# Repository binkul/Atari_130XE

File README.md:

# Schema of Atari 130XE C070067 REV B
# 2 x 4464 (4 bit RAM)

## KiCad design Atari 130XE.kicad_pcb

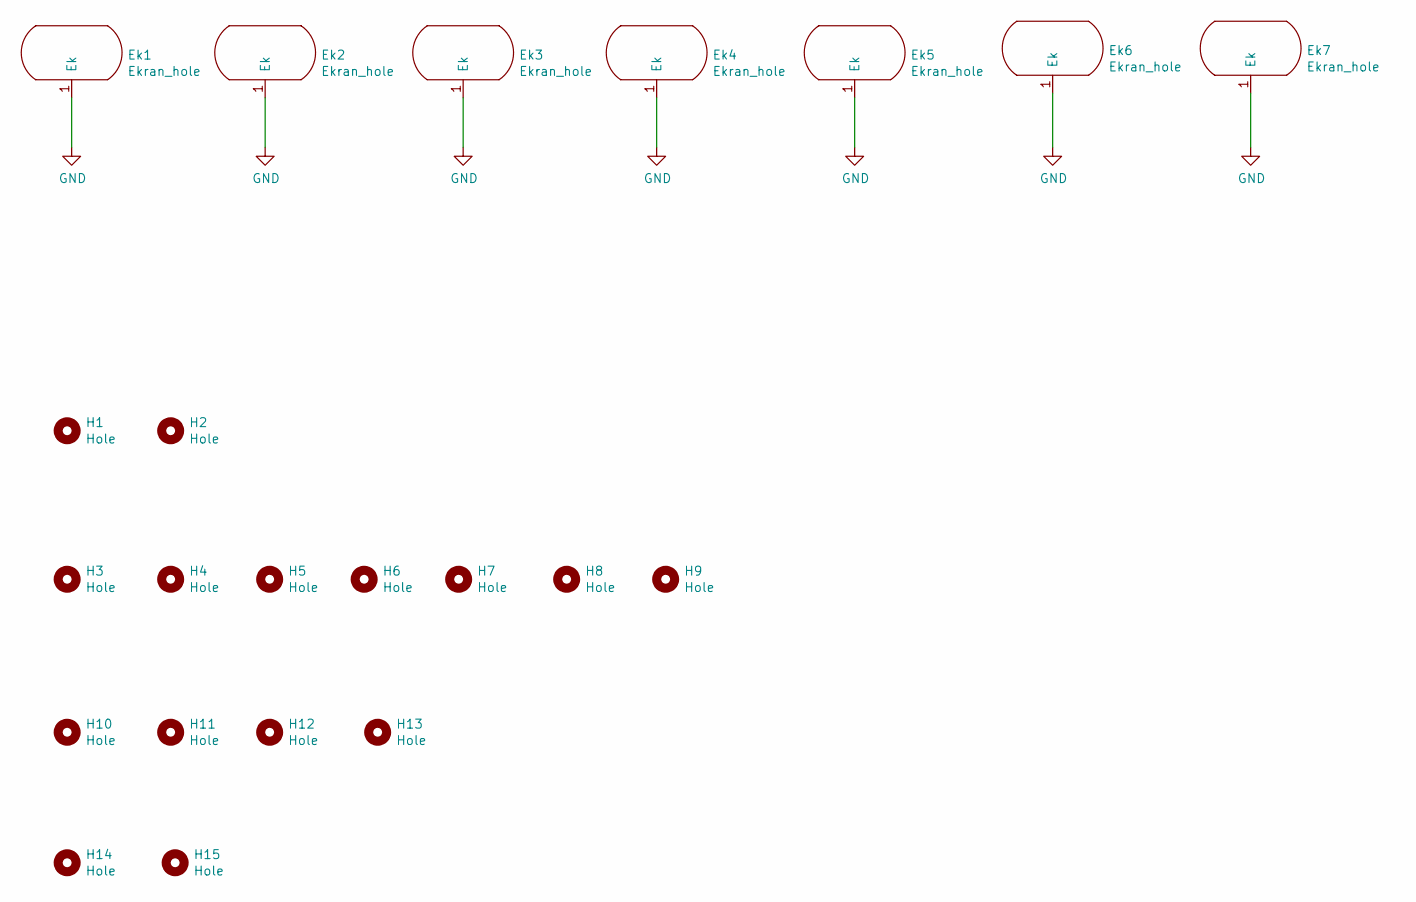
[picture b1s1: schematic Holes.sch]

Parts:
Ek1, Ek2, Ek3, Ek4, Ek5, Ek6, Ek7: Ekran_hole; Ekran_GND
H1, H2: Hole; Medium_hole
H3, H4, H5, H6, H7, H8, H9: Hole; Hole_3.4mm
H10, H11, H12, H13: Hole; Hole_4.4mm
H14, H15: Hole; MountingHole_4.5mm

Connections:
GND: Ek1.1, Ek2.1, Ek3.1, Ek4.1, Ek5.1, Ek6.1, Ek7.1; also elsewhere on the board

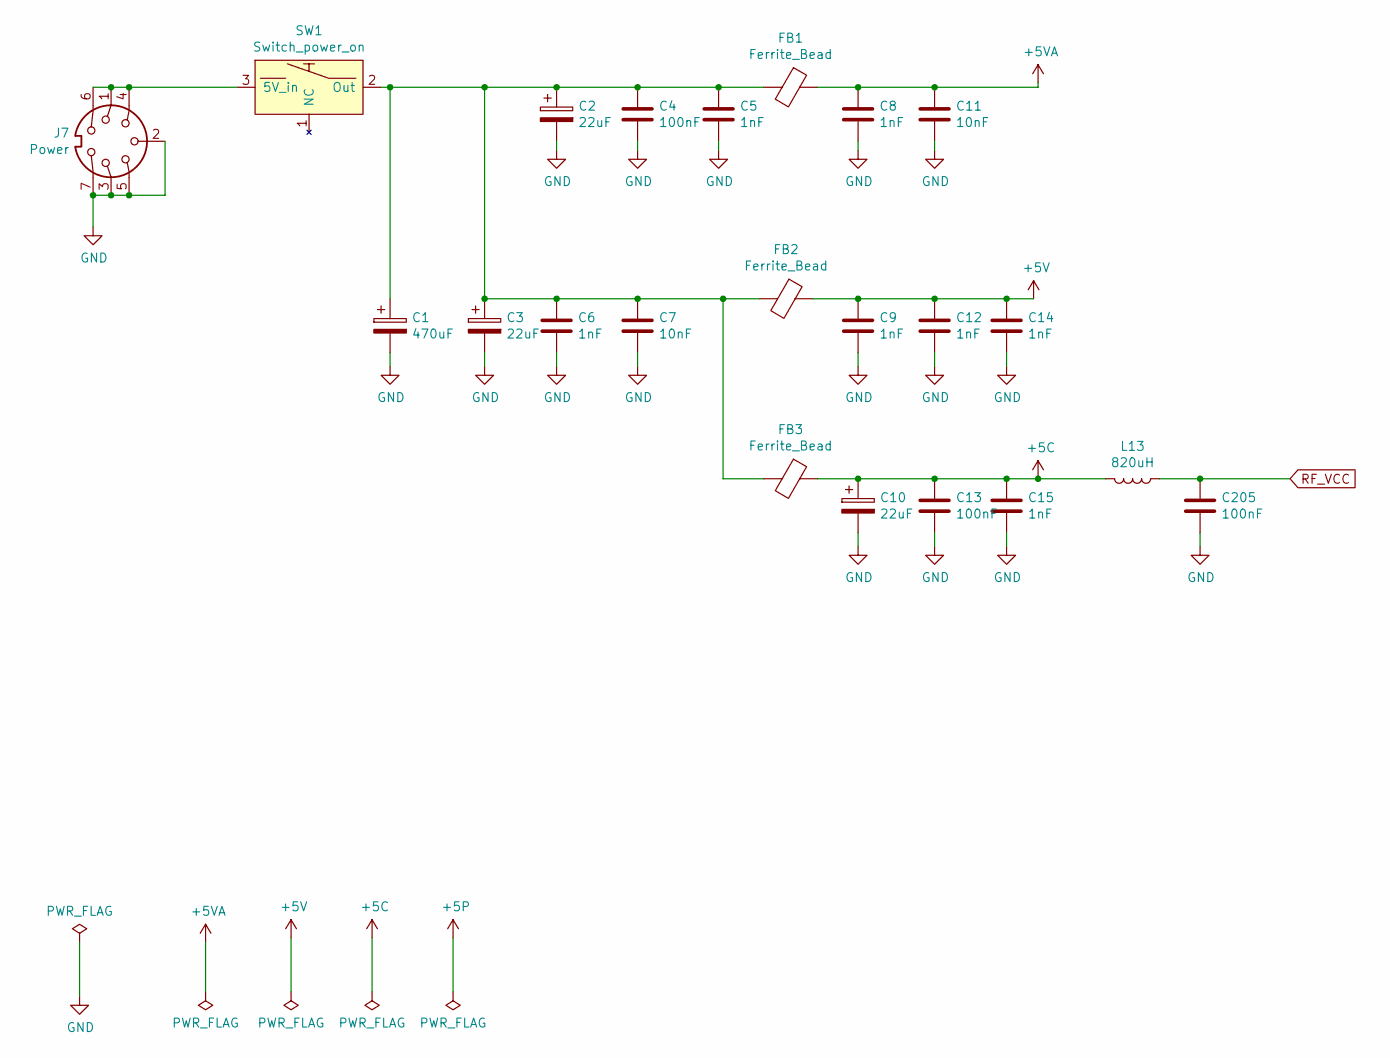
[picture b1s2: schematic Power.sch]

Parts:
C1: 470uF; CP_Radial_D8.0mm_P3.80mm
C2, C3, C10: 22uF; CP_Radial_D6.3mm_P2.50mm
C4, C13, C205: 100nF; C_Axial_L5.1mm_D2.5mm_P12.50mm_Horizontal
C5, C6, C8, C9, C12, C14, C15: 1nF; C_Axial_L5.1mm_D2.5mm_P12.50mm_Horizontal
C7, C11: 10nF; C_Axial_L5.1mm_D2.5mm_P12.50mm_Horizontal
FB1, FB2, FB3: Ferrite_Bead; L_Axial_L7.0mm_D3.3mm_P12.50mm_Horizontal_Fastron_MICC
J7: Power; DIN_7_pin
L13: 820uH; L_Axial_L7.0mm_D3.3mm_P12.50mm_Horizontal_Fastron_MICC
SW1: Switch_power_on; Switch_ON-OFF

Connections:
+5C: C10.1, C13.1, C15.1, FB3.1, L13.2; also elsewhere on the board
+5V: C9.1, C12.1, C14.1, FB2.1
+5VA: C8.1, C11.1, FB1.1; also elsewhere on the board
GND: C1.2, C2.2, C3.2, C4.2, C5.2, C6.2, C7.2, C8.2, C9.2, C10.2, C11.2, C12.2, C13.2, C14.2, C15.2, C205.2, J7.2, J7.3, J7.5, J7.7; also elsewhere on the board
unnamed: C1.1, C2.1, C3.1, C4.1, C5.1, C6.1, C7.1, FB1.2, FB2.2, FB3.2, SW1.2 (Out)
unnamed: J7.1, J7.4, J7.6, SW1.3 (5V_in)
RF_VCC: C205.1, L13.1; also elsewhere on the board

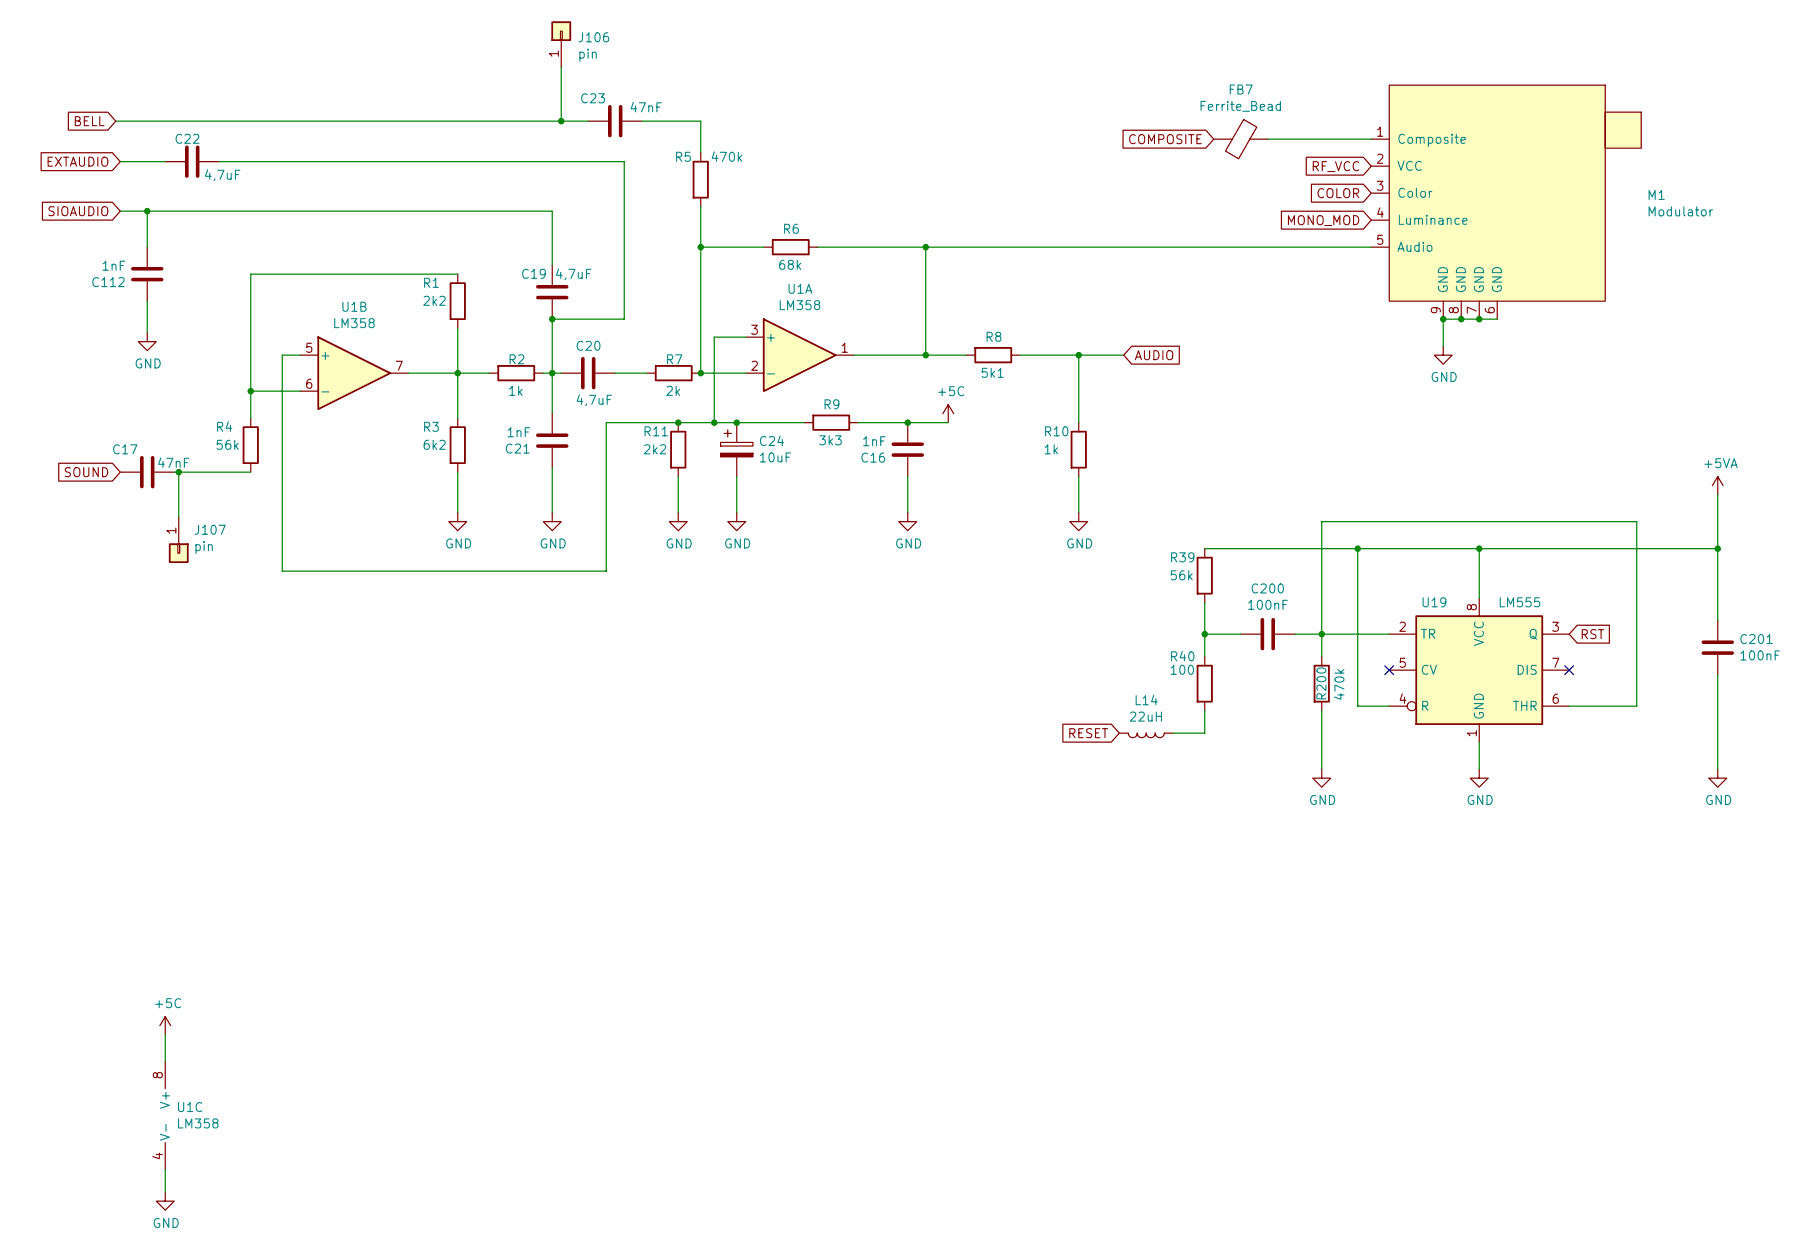
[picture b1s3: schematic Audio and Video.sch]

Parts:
C16, C21, C112: 1nF; C_Axial_L5.1mm_D2.5mm_P12.50mm_Horizontal
C17, C23: 47nF; C_Axial_L5.1mm_D2.5mm_P12.50mm_Horizontal
C19, C20, C22: 4,7uF; CP_Radial_D8.0mm_P3.50mm
C24: 10uF; CP_Axial_L11.0mm_D6.0mm_P18.00mm_Horizontal
C200, C201: 100nF; C_Axial_L5.1mm_D2.5mm_P12.50mm_Horizontal
FB7: Ferrite_Bead; L_Axial_L7.0mm_D3.3mm_P12.50mm_Horizontal_Fastron_MICC
J106, J107: pin; PinHeader_1x01_P2.00mm_Vertical
L14: 22uH; L_Axial_L7.0mm_D3.3mm_P12.50mm_Horizontal_Fastron_MICC
M1: Modulator; Modulator_TV
R1, R11: 2k2; R_Axial_DIN0207_L3.6mm_D2.2mm_P10.16mm_Horizontal
R2, R10: 1k; R_Axial_DIN0207_L3.6mm_D2.2mm_P10.16mm_Horizontal
R3: 6k2; R_Axial_DIN0207_L3.6mm_D2.2mm_P10.16mm_Horizontal
R4, R39: 56k; R_Axial_DIN0207_L3.6mm_D2.2mm_P10.16mm_Horizontal
R5, R200: 470k; R_Axial_DIN0207_L3.6mm_D2.2mm_P10.16mm_Horizontal
R6: 68k; R_Axial_DIN0207_L3.6mm_D2.2mm_P10.16mm_Horizontal
R7: 2k; R_Axial_DIN0207_L3.6mm_D2.2mm_P10.16mm_Horizontal
R8: 5k1; R_Axial_DIN0207_L3.6mm_D2.2mm_P10.16mm_Horizontal
R9: 3k3; R_Axial_DIN0207_L3.6mm_D2.2mm_P10.16mm_Horizontal
R40: 100; R_Axial_DIN0207_L3.6mm_D2.2mm_P10.16mm_Horizontal
U1: LM358; DIP-8_W7.62mm_Socket
U19: LM555; DIP-8_W7.62mm_Socket

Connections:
+5C: C16.2, R9.1, U1.8 (V+); also elsewhere on the board
+5VA: C201.1, R39.1, U19.4 (R), U19.8 (VCC); also elsewhere on the board
AUDIO: R8.1, R10.1; also elsewhere on the board
BELL: C23.2, J106.1; also elsewhere on the board
COLOR: M1.3 (Color); also elsewhere on the board
COMPOSITE: FB7.2; also elsewhere on the board
EXTAUDIO: C22.1; also elsewhere on the board
GND: C16.1, C21.1, C24.2, C112.1, C201.2, M1.6 (GND), M1.7 (GND), M1.8 (GND), M1.9 (GND), R3.2, R10.2, R11.2, R200.2, U1.4 (V-), U19.1 (GND); also elsewhere on the board
MONO_MOD: M1.4 (Luminance); also elsewhere on the board
unnamed: C17.1, J107.1, R4.2
unnamed: C19.1, C20.2, C21.2, C22.2, R2.1
unnamed: C20.1, R7.2
unnamed: C23.1, R5.1
unnamed: C24.1, R9.2, R11.1, U1.3 (+), U1.5 (+)
unnamed: C200.1, R200.1, U19.2 (TR), U19.6 (THR)
unnamed: C200.2, R39.2, R40.1
unnamed: FB7.1, M1.1 (Composite)
unnamed: L14.1, R40.2
unnamed: M1.5 (Audio), R6.1, R8.2, U1.1
unnamed: R1.1, R4.1, U1.6 (-)
unnamed: R1.2, R2.2, R3.1, U1.7
unnamed: R5.2, R6.2, R7.1, U1.2 (-)
RESET: L14.2; also elsewhere on the board
RF_VCC: M1.2 (VCC); also elsewhere on the board
RST: U19.3 (Q); also elsewhere on the board
SIOAUDIO: C19.2, C112.2; also elsewhere on the board
SOUND: C17.2; also elsewhere on the board

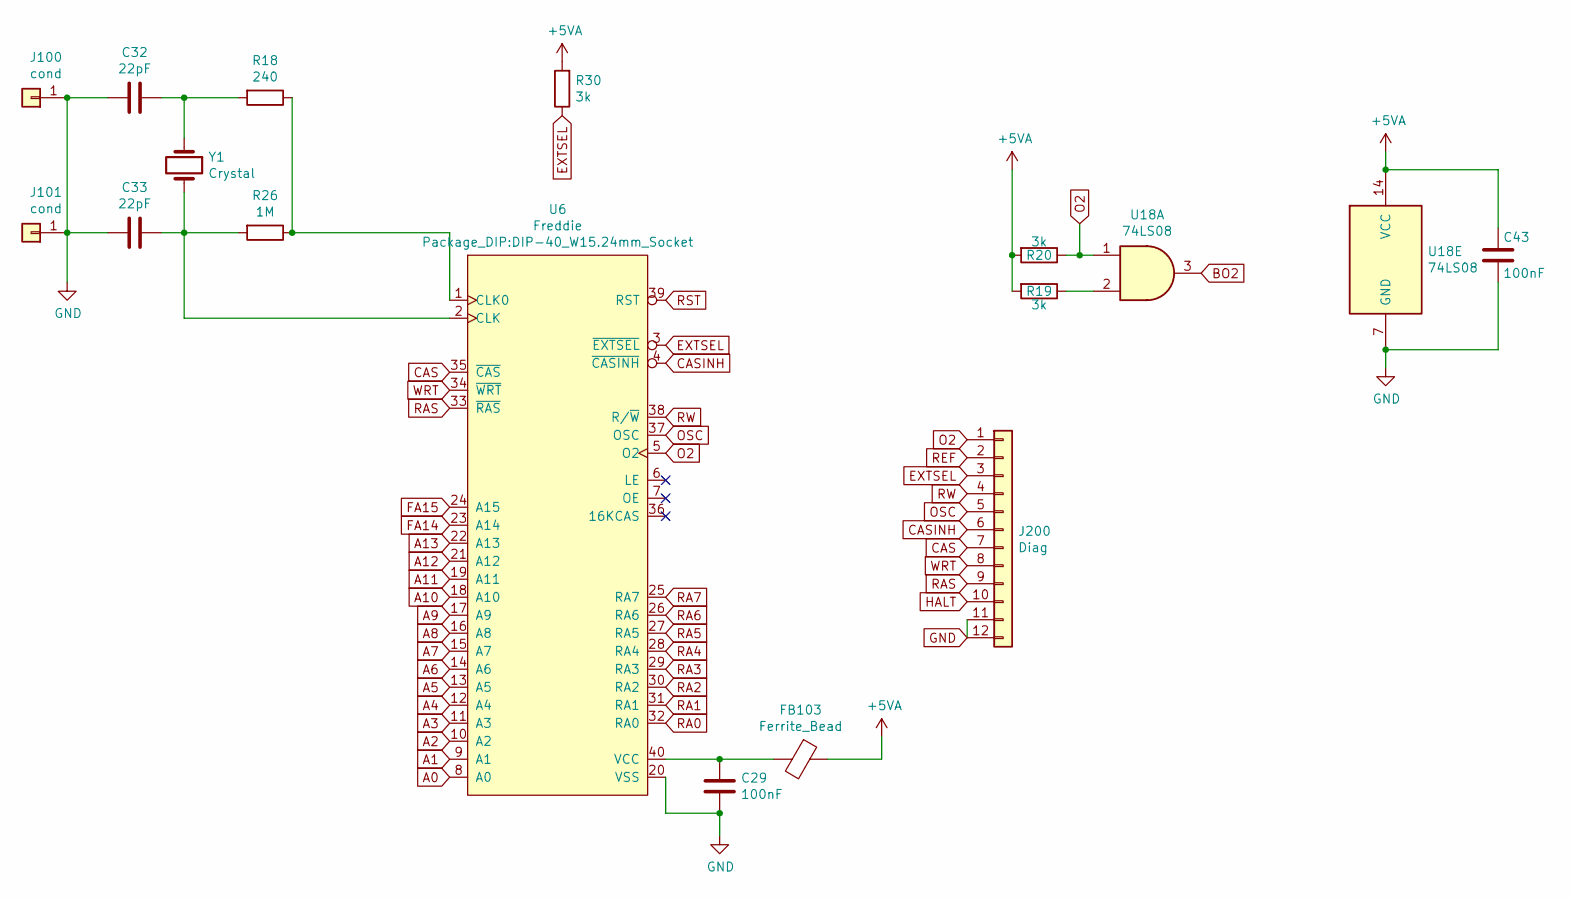
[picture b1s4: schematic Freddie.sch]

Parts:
C29, C43: 100nF; C_Axial_L5.1mm_D2.5mm_P12.50mm_Horizontal
C32, C33: 22pF; C_Axial_L5.1mm_D2.5mm_P12.50mm_Horizontal
FB103: Ferrite_Bead; L_Axial_L7.0mm_D3.3mm_P12.50mm_Horizontal_Fastron_MICC
J100, J101: cond; PinHeader_1x01_P2.00mm_Vertical
J200: Diag; PinHeader_1x12_P2.54mm_Vertical
R18: 240; R_Axial_DIN0207_L6.3mm_D2.5mm_P10.16mm_Horizontal
R19, R20, R30: 3k; R_Axial_DIN0207_L3.6mm_D2.2mm_P10.16mm_Horizontal
R26: 1M; R_Axial_DIN0207_L6.3mm_D2.5mm_P10.16mm_Horizontal
U6: Freddie; DIP-40_W15.24mm_Socket
U18: 74LS08; DIP-14_W7.62mm_Socket
Y1: Crystal; Crystal_HC18-U_Vertical

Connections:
+5VA: C43.1, FB103.1, R19.2, R20.2, R30.2, U18.14 (VCC); also elsewhere on the board
A0: U6.8 (A0); also elsewhere on the board
A1: U6.9 (A1); also elsewhere on the board
A2: U6.10 (A2); also elsewhere on the board
A3: U6.11 (A3); also elsewhere on the board
A4: U6.12 (A4); also elsewhere on the board
A5: U6.13 (A5); also elsewhere on the board
A6: U6.14 (A6); also elsewhere on the board
A7: U6.15 (A7); also elsewhere on the board
A8: U6.16 (A8); also elsewhere on the board
A9: U6.17 (A9); also elsewhere on the board
A10: U6.18 (A10); also elsewhere on the board
A11: U6.19 (A11); also elsewhere on the board
A12: U6.21 (A12); also elsewhere on the board
A13: U6.22 (A13); also elsewhere on the board
BO2: U18.3; also elsewhere on the board
CAS: J200.7, U6.35 (~CAS); also elsewhere on the board
CASINH: J200.6, U6.4 (~CASINH); also elsewhere on the board
EXTSEL: J200.3, R30.1, U6.3 (~EXTSEL); also elsewhere on the board
FA14: U6.23 (A14); also elsewhere on the board
FA15: U6.24 (A15); also elsewhere on the board
GND: C29.2, C32.2, C33.2, C43.2, J100.1, J101.1, J200.11, J200.12, U6.20 (VSS), U18.7 (GND); also elsewhere on the board
HALT: J200.10; also elsewhere on the board
unnamed: C29.1, FB103.2, U6.40 (VCC)
unnamed: C32.1, R18.2, Y1.1
unnamed: C33.1, R26.2, U6.2 (CLK), Y1.2
unnamed: R18.1, R26.1, U6.1 (CLK0)
unnamed: R19.1, U18.2
O2: J200.1, R20.1, U6.5 (O2), U18.1; also elsewhere on the board
OSC: J200.5, U6.37 (OSC); also elsewhere on the board
RA0: U6.32 (RA0); also elsewhere on the board
RA1: U6.31 (RA1); also elsewhere on the board
RA2: U6.30 (RA2); also elsewhere on the board
RA3: U6.29 (RA3); also elsewhere on the board
RA4: U6.28 (RA4); also elsewhere on the board
RA5: U6.27 (RA5); also elsewhere on the board
RA6: U6.26 (RA6); also elsewhere on the board
RA7: U6.25 (RA7); also elsewhere on the board
RAS: J200.9, U6.33 (~RAS); also elsewhere on the board
REF: J200.2; also elsewhere on the board
RST: U6.39 (RST); also elsewhere on the board
RW: J200.4, U6.38 (R/~W); also elsewhere on the board
WRT: J200.8, U6.34 (~WRT); also elsewhere on the board

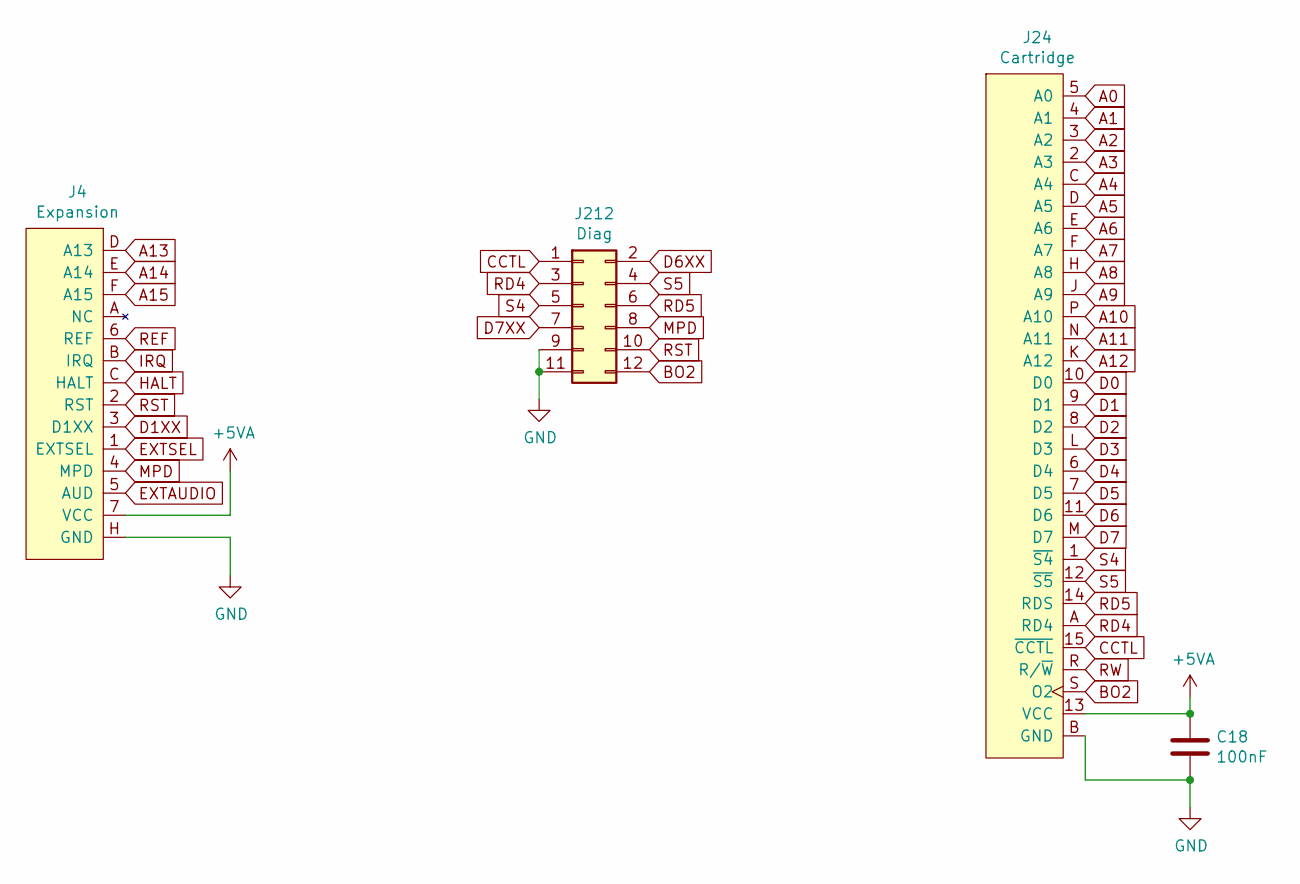
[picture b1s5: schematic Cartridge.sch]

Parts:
C18: 100nF; C_Axial_L5.1mm_D2.5mm_P12.50mm_Horizontal
J4: Expansion; Expansion_Slot
J24: Cartridge; Cartridge_Slot
J212: Diag; PinHeader_2x06_P2.54mm_Vertical

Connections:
+5VA: C18.1, J4.7 (VCC), J24.13 (VCC); also elsewhere on the board
A0: J24.5 (A0); also elsewhere on the board
A1: J24.4 (A1); also elsewhere on the board
A2: J24.3 (A2); also elsewhere on the board
A3: J24.2 (A3); also elsewhere on the board
A4: J24.C (A4); also elsewhere on the board
A5: J24.D (A5); also elsewhere on the board
A6: J24.E (A6); also elsewhere on the board
A7: J24.F (A7); also elsewhere on the board
A8: J24.H (A8); also elsewhere on the board
A9: J24.J (A9); also elsewhere on the board
A10: J24.P (A10); also elsewhere on the board
A11: J24.N (A11); also elsewhere on the board
A12: J24.K (A12); also elsewhere on the board
A13: J4.D (A13); also elsewhere on the board
A14: J4.E (A14); also elsewhere on the board
A15: J4.F (A15); also elsewhere on the board
BO2: J24.S (O2), J212.12; also elsewhere on the board
CCTL: J24.15 (~CCTL), J212.1; also elsewhere on the board
D0: J24.10 (D0); also elsewhere on the board
D1: J24.9 (D1); also elsewhere on the board
D1XX: J4.3 (D1XX); also elsewhere on the board
D2: J24.8 (D2); also elsewhere on the board
D3: J24.L (D3); also elsewhere on the board
D4: J24.6 (D4); also elsewhere on the board
D5: J24.7 (D5); also elsewhere on the board
D6: J24.11 (D6); also elsewhere on the board
D6XX: J212.2; also elsewhere on the board
D7: J24.M (D7); also elsewhere on the board
D7XX: J212.7; also elsewhere on the board
EXTAUDIO: J4.5 (AUD); also elsewhere on the board
EXTSEL: J4.1 (EXTSEL); also elsewhere on the board
GND: C18.2, J4.H (GND), J24.B (GND), J212.9, J212.11; also elsewhere on the board
HALT: J4.C (HALT); also elsewhere on the board
IRQ: J4.B (IRQ); also elsewhere on the board
MPD: J4.4 (MPD), J212.8; also elsewhere on the board
RD4: J24.A (RD4), J212.3; also elsewhere on the board
RD5: J24.14 (RDS), J212.6; also elsewhere on the board
REF: J4.6 (REF); also elsewhere on the board
RST: J4.2 (RST), J212.10; also elsewhere on the board
RW: J24.R (R/~W); also elsewhere on the board
S4: J24.1 (~S4), J212.5; also elsewhere on the board
S5: J24.12 (~S5), J212.4; also elsewhere on the board

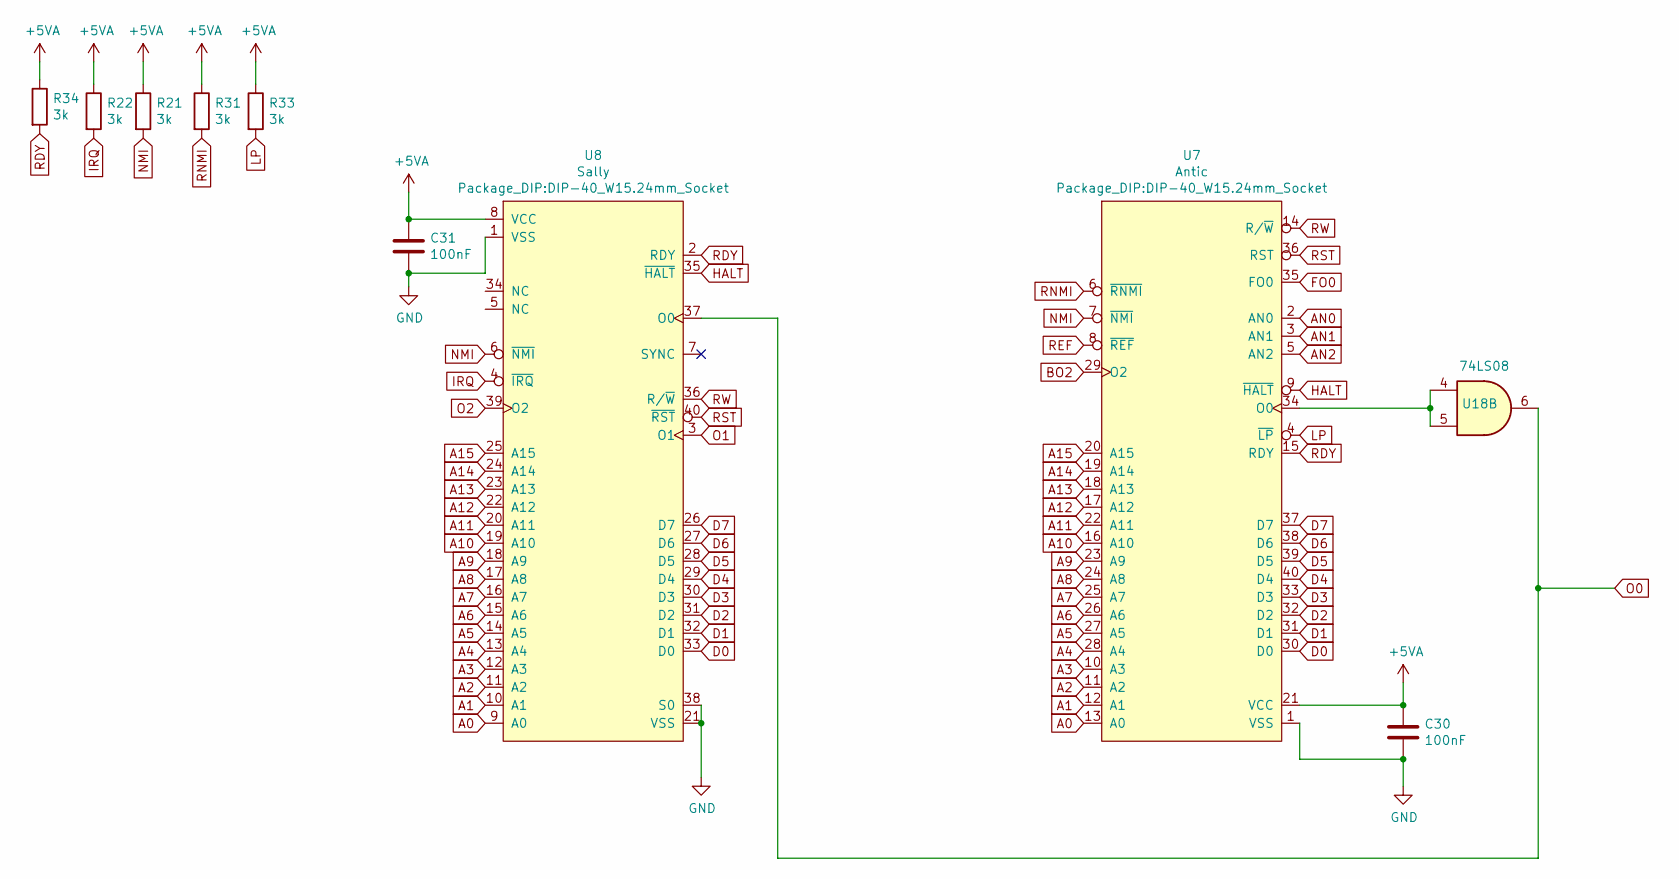
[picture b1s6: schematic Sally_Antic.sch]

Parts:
C30, C31: 100nF; C_Axial_L5.1mm_D2.5mm_P12.50mm_Horizontal
R21, R22, R31, R33, R34: 3k; R_Axial_DIN0207_L3.6mm_D2.2mm_P10.16mm_Horizontal
U7: Antic; DIP-40_W15.24mm_Socket
U8: Sally; DIP-40_W15.24mm_Socket
U18: 74LS08; DIP-14_W7.62mm_Socket

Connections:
+5VA: C30.1, C31.1, R21.1, R22.1, R31.1, R33.1, R34.1, U7.21 (VCC), U8.8 (VCC); also elsewhere on the board
A0: U7.13 (A0), U8.9 (A0); also elsewhere on the board
A1: U7.12 (A1), U8.10 (A1); also elsewhere on the board
A2: U7.11 (A2), U8.11 (A2); also elsewhere on the board
A3: U7.10 (A3), U8.12 (A3); also elsewhere on the board
A4: U7.28 (A4), U8.13 (A4); also elsewhere on the board
A5: U7.27 (A5), U8.14 (A5); also elsewhere on the board
A6: U7.26 (A6), U8.15 (A6); also elsewhere on the board
A7: U7.25 (A7), U8.16 (A7); also elsewhere on the board
A8: U7.24 (A8), U8.17 (A8); also elsewhere on the board
A9: U7.23 (A9), U8.18 (A9); also elsewhere on the board
A10: U7.16 (A10), U8.19 (A10); also elsewhere on the board
A11: U7.22 (A11), U8.20 (A11); also elsewhere on the board
A12: U7.17 (A12), U8.22 (A12); also elsewhere on the board
A13: U7.18 (A13), U8.23 (A13); also elsewhere on the board
A14: U7.19 (A14), U8.24 (A14); also elsewhere on the board
A15: U7.20 (A15), U8.25 (A15); also elsewhere on the board
AN0: U7.2 (AN0); also elsewhere on the board
AN1: U7.3 (AN1); also elsewhere on the board
AN2: U7.5 (AN2); also elsewhere on the board
BO2: U7.29 (O2); also elsewhere on the board
D0: U7.30 (D0), U8.33 (D0); also elsewhere on the board
D1: U7.31 (D1), U8.32 (D1); also elsewhere on the board
D2: U7.32 (D2), U8.31 (D2); also elsewhere on the board
D3: U7.33 (D3), U8.30 (D3); also elsewhere on the board
D4: U7.40 (D4), U8.29 (D4); also elsewhere on the board
D5: U7.39 (D5), U8.28 (D5); also elsewhere on the board
D6: U7.38 (D6), U8.27 (D6); also elsewhere on the board
D7: U7.37 (D7), U8.26 (D7); also elsewhere on the board
FO0: U7.35 (FO0); also elsewhere on the board
GND: C30.2, C31.2, U7.1 (VSS), U8.1 (VSS), U8.21 (VSS), U8.38 (S0); also elsewhere on the board
HALT: U7.9 (~HALT), U8.35 (~HALT); also elsewhere on the board
IRQ: R22.2, U8.4 (~IRQ); also elsewhere on the board
LP: R33.2, U7.4 (~LP); also elsewhere on the board
NMI: R21.2, U7.7 (~NMI), U8.6 (~NMI)
unnamed: U7.34 (O0), U18.4, U18.5
O0: U8.37 (O0), U18.6
O1: U8.3 (O1); also elsewhere on the board
O2: U8.39 (O2); also elsewhere on the board
RDY: R34.2, U7.15 (RDY), U8.2 (RDY)
REF: U7.8 (~REF); also elsewhere on the board
RNMI: R31.2, U7.6 (~RNMI)
RST: U7.36 (RST), U8.40 (~RST); also elsewhere on the board
RW: U7.14 (R/~W), U8.36 (R/~W); also elsewhere on the board

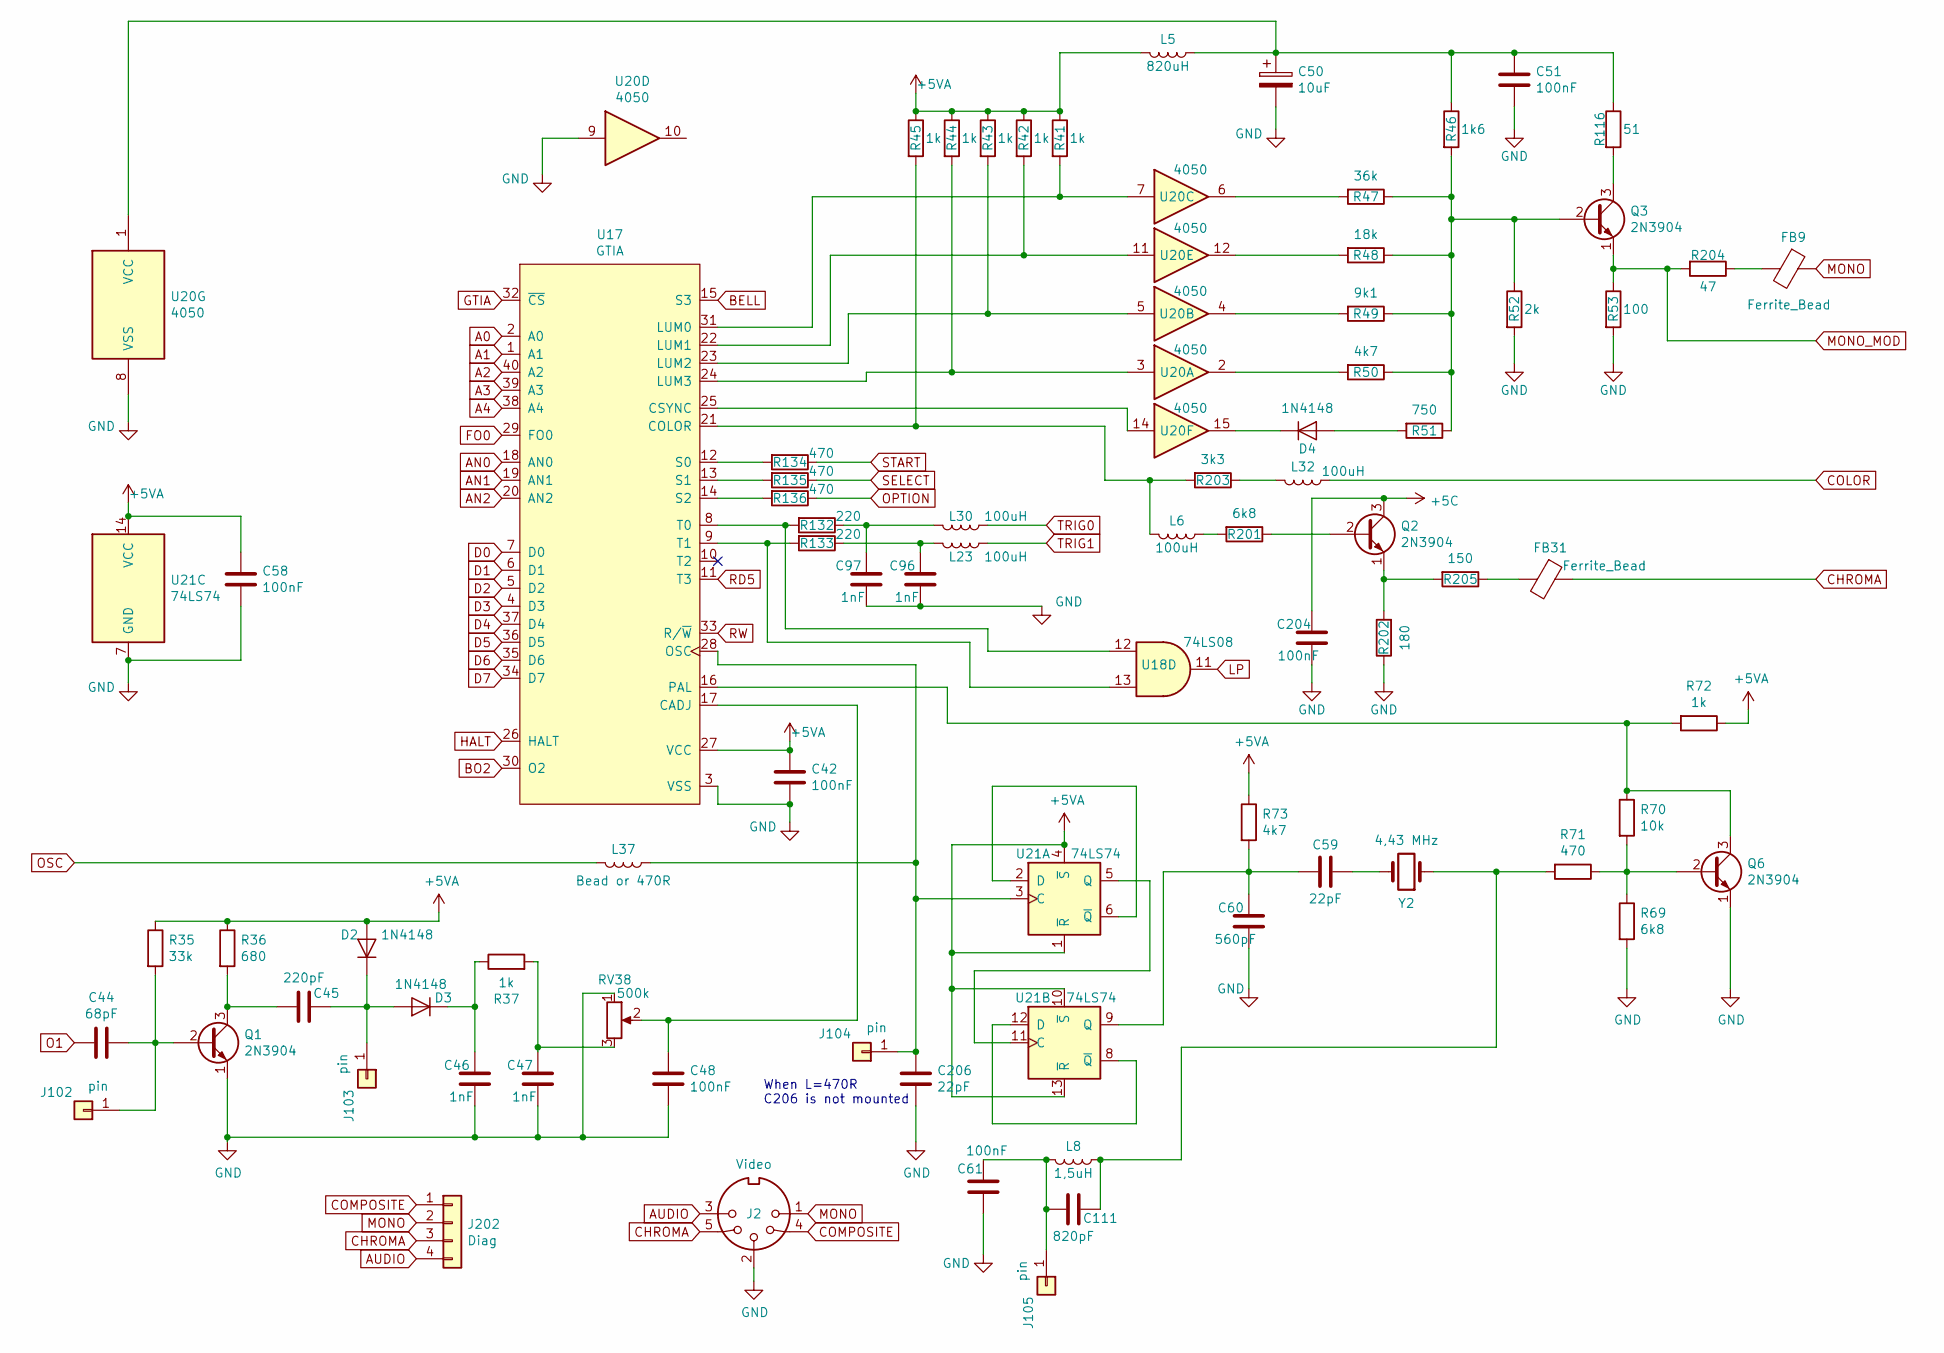
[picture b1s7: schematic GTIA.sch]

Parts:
C42, C48, C51, C58, C61, C204: 100nF; C_Axial_L5.1mm_D2.5mm_P12.50mm_Horizontal
C44: 68pF; C_Axial_L5.1mm_D2.5mm_P12.50mm_Horizontal
C45: 220pF; C_Axial_L5.1mm_D2.5mm_P12.50mm_Horizontal
C46, C47, C96, C97: 1nF; C_Axial_L5.1mm_D2.5mm_P12.50mm_Horizontal
C50: 10uF; CP_Radial_D5.0mm_P2.00mm
C59, C206: 22pF; C_Axial_L5.1mm_D2.5mm_P12.50mm_Horizontal
C60: 560pF; C_Axial_L5.1mm_D2.5mm_P12.50mm_Horizontal
C111: 820pF; C_Axial_L5.1mm_D2.5mm_P12.50mm_Horizontal
D2, D3, D4: 1N4148; D_DO-35_SOD27_P12.70mm_Horizontal
FB9, FB31: Ferrite_Bead; L_Axial_L7.0mm_D3.3mm_P12.50mm_Horizontal_Fastron_MICC
J2: Video; DIN_5_pin
J102, J103, J104, J105: pin; PinHeader_1x01_P2.00mm_Vertical
J202: Diag; PinHeader_1x04_P2.54mm_Vertical
L5: 820uH; L_Axial_L7.0mm_D3.3mm_P12.50mm_Horizontal_Fastron_MICC
L6, L23, L30, L32: 100uH; L_Axial_L7.0mm_D3.3mm_P12.50mm_Horizontal_Fastron_MICC
L8: 1,5uH; L_Axial_L7.0mm_D3.3mm_P12.50mm_Horizontal_Fastron_MICC
L37: Bead or 470R; L_Axial_L7.0mm_D3.3mm_P12.50mm_Horizontal_Fastron_MICC
Q1, Q2, Q3: 2N3904; TO-92L_Wide
Q6: 2N3904; TO-92
R35: 33k; R_Axial_DIN0207_L3.6mm_D2.2mm_P10.16mm_Horizontal
R36: 680; R_Axial_DIN0207_L3.6mm_D2.2mm_P10.16mm_Horizontal
R37, R41, R42, R43, R44, R45, R72: 1k; R_Axial_DIN0207_L3.6mm_D2.2mm_P10.16mm_Horizontal
R46: 1k6; R_Axial_DIN0207_L3.6mm_D2.2mm_P10.16mm_Horizontal
R47: 36k; R_Axial_DIN0207_L3.6mm_D2.2mm_P10.16mm_Horizontal
R48: 18k; R_Axial_DIN0207_L3.6mm_D2.2mm_P10.16mm_Horizontal
R49: 9k1; R_Axial_DIN0207_L3.6mm_D2.2mm_P10.16mm_Horizontal
R50, R73: 4k7; R_Axial_DIN0207_L3.6mm_D2.2mm_P10.16mm_Horizontal
R51: 750; R_Axial_DIN0207_L3.6mm_D2.2mm_P10.16mm_Horizontal
R52: 2k; R_Axial_DIN0207_L3.6mm_D2.2mm_P10.16mm_Horizontal
R53: 100; R_Axial_DIN0207_L3.6mm_D2.2mm_P10.16mm_Horizontal
R69, R201: 6k8; R_Axial_DIN0207_L3.6mm_D2.2mm_P10.16mm_Horizontal
R70: 10k; R_Axial_DIN0207_L3.6mm_D2.2mm_P10.16mm_Horizontal
R71, R134, R135, R136: 470; R_Axial_DIN0207_L3.6mm_D2.2mm_P10.16mm_Horizontal
R116: 51; R_Axial_DIN0207_L3.6mm_D2.2mm_P10.16mm_Horizontal
R132, R133: 220; R_Axial_DIN0207_L3.6mm_D2.2mm_P10.16mm_Horizontal
R202: 180; R_Axial_DIN0207_L3.6mm_D2.2mm_P10.16mm_Horizontal
R203: 3k3; R_Axial_DIN0207_L3.6mm_D2.2mm_P10.16mm_Horizontal
R204: 47; R_Axial_DIN0207_L3.6mm_D2.2mm_P10.16mm_Horizontal
R205: 150; R_Axial_DIN0207_L3.6mm_D2.2mm_P10.16mm_Horizontal
RV38: 500k; Potentiometer_ACP_CA9-V10_Vertical_Hole
U17: GTIA; DIP-40_W15.24mm_Socket
U18: 74LS08; DIP-14_W7.62mm_Socket
U20: 4050; DIP-16_W7.62mm_Socket
U21: 74LS74; DIP-14_W7.62mm_Socket
Y2: 4,43 MHz; Crystal_HC18-U_Horizontal

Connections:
+5C: C204.2, Q2.3 (C); also elsewhere on the board
+5VA: C42.1, C58.1, D2.2 (A), L5.2, R35.1, R36.1, R41.1, R42.1, R43.1, R44.1, R45.1, R72.1, R73.1, U17.27 (VCC), U21.1 (~R), U21.4 (~S), U21.10 (~S), U21.13 (~R), U21.14 (VCC); also elsewhere on the board
A0: U17.2 (A0); also elsewhere on the board
A1: U17.1 (A1); also elsewhere on the board
A2: U17.40 (A2); also elsewhere on the board
A3: U17.39 (A3); also elsewhere on the board
A4: U17.38 (A4); also elsewhere on the board
AN0: U17.18 (AN0); also elsewhere on the board
AN1: U17.19 (AN1); also elsewhere on the board
AN2: U17.20 (AN2); also elsewhere on the board
AUDIO: J2.3, J202.4; also elsewhere on the board
BELL: U17.15 (S3); also elsewhere on the board
BO2: U17.30 (O2); also elsewhere on the board
CHROMA: FB31.1, J2.5, J202.3
COLOR: L32.1; also elsewhere on the board
COMPOSITE: J2.4, J202.1; also elsewhere on the board
D0: U17.7 (D0); also elsewhere on the board
D1: U17.6 (D1); also elsewhere on the board
D2: U17.5 (D2); also elsewhere on the board
D3: U17.4 (D3); also elsewhere on the board
D4: U17.37 (D4); also elsewhere on the board
D5: U17.36 (D5); also elsewhere on the board
D6: U17.35 (D6); also elsewhere on the board
D7: U17.34 (D7); also elsewhere on the board
FO0: U17.29 (FO0); also elsewhere on the board
GND: C42.2, C46.1, C47.1, C48.1, C50.2, C51.2, C58.2, C60.1, C61.1, C96.1, C97.1, C204.1, C206.1, J2.2, Q1.1 (E), Q6.1 (E), R52.2, R53.2, R69.2, R202.1, RV38.1, U17.3 (VSS), U20.8 (VSS), U20.9, U21.7 (GND); also elsewhere on the board
GTIA: U17.32 (~CS); also elsewhere on the board
HALT: U17.26 (HALT); also elsewhere on the board
LP: U18.11; also elsewhere on the board
MONO: FB9.1, J2.1, J202.2
MONO_MOD: Q3.1 (E), R53.1, R204.2; also elsewhere on the board
unnamed: C44.1, J102.1, Q1.2 (B), R35.2
unnamed: C45.1, D2.1 (K), D3.2 (A), J103.1
unnamed: C45.2, Q1.3 (C), R36.2
unnamed: C46.2, D3.1 (K), R37.1
unnamed: C47.2, R37.2, RV38.3
unnamed: C48.2, RV38.2, U17.17 (CADJ)
unnamed: C50.1, C51.1, L5.1, R46.1, R116.1, U20.1 (VCC)
unnamed: C59.1, C60.2, R73.2, U21.9 (Q)
unnamed: C59.2, Y2.2
unnamed: C96.2, L23.2, R133.1
unnamed: C97.2, L30.2, R132.1
unnamed: C111.1, L8.1, R71.2, Y2.1
unnamed: C61.2, C111.2, J105.1, L8.2
unnamed: C206.2, J104.1, L37.1, U17.28 (OSC), U21.3 (C)
unnamed: D4.1 (K), U20.15
unnamed: D4.2 (A), R51.2
unnamed: FB9.2, R204.1
unnamed: FB31.2, R205.1
unnamed: L6.1, R201.2
unnamed: L6.2, R45.2, R203.2, U17.21 (COLOR)
unnamed: L32.2, R203.1
unnamed: Q2.1 (E), R202.2, R205.2
unnamed: Q2.2 (B), R201.1
unnamed: Q3.2 (B), R46.2, R47.1, R48.1, R49.1, R50.1, R51.1, R52.1
unnamed: Q3.3 (C), R116.2
unnamed: Q6.2 (B), R69.1, R70.2, R71.1
unnamed: Q6.3 (C), R70.1, R72.2, U17.16 (PAL)
unnamed: R41.2, U17.31 (LUM0), U20.7
unnamed: R42.2, U17.22 (LUM1), U20.11
unnamed: R43.2, U17.23 (LUM2), U20.5
unnamed: R44.2, U17.24 (LUM3), U20.3
unnamed: R47.2, U20.6
unnamed: R48.2, U20.12
unnamed: R49.2, U20.4
unnamed: R50.2, U20.2
unnamed: R132.2, U17.8 (T0), U18.12
unnamed: R133.2, U17.9 (T1), U18.13
unnamed: R134.2, U17.12 (S0)
unnamed: R135.2, U17.13 (S1)
unnamed: R136.2, U17.14 (S2)
unnamed: U17.25 (CSYNC), U20.14
unnamed: U21.2 (D), U21.6 (~Q)
unnamed: U21.5 (Q), U21.11 (C)
unnamed: U21.8 (~Q), U21.12 (D)
O1: C44.2; also elsewhere on the board
OPTION: R136.1; also elsewhere on the board
OSC: L37.2; also elsewhere on the board
RD5: U17.11 (T3); also elsewhere on the board
RW: U17.33 (R/~W); also elsewhere on the board
SELECT: R135.1; also elsewhere on the board
START: R134.1; also elsewhere on the board
TRIG0: L30.1; also elsewhere on the board
TRIG1: L23.1; also elsewhere on the board

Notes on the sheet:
When L=470R C206 is not mounted
